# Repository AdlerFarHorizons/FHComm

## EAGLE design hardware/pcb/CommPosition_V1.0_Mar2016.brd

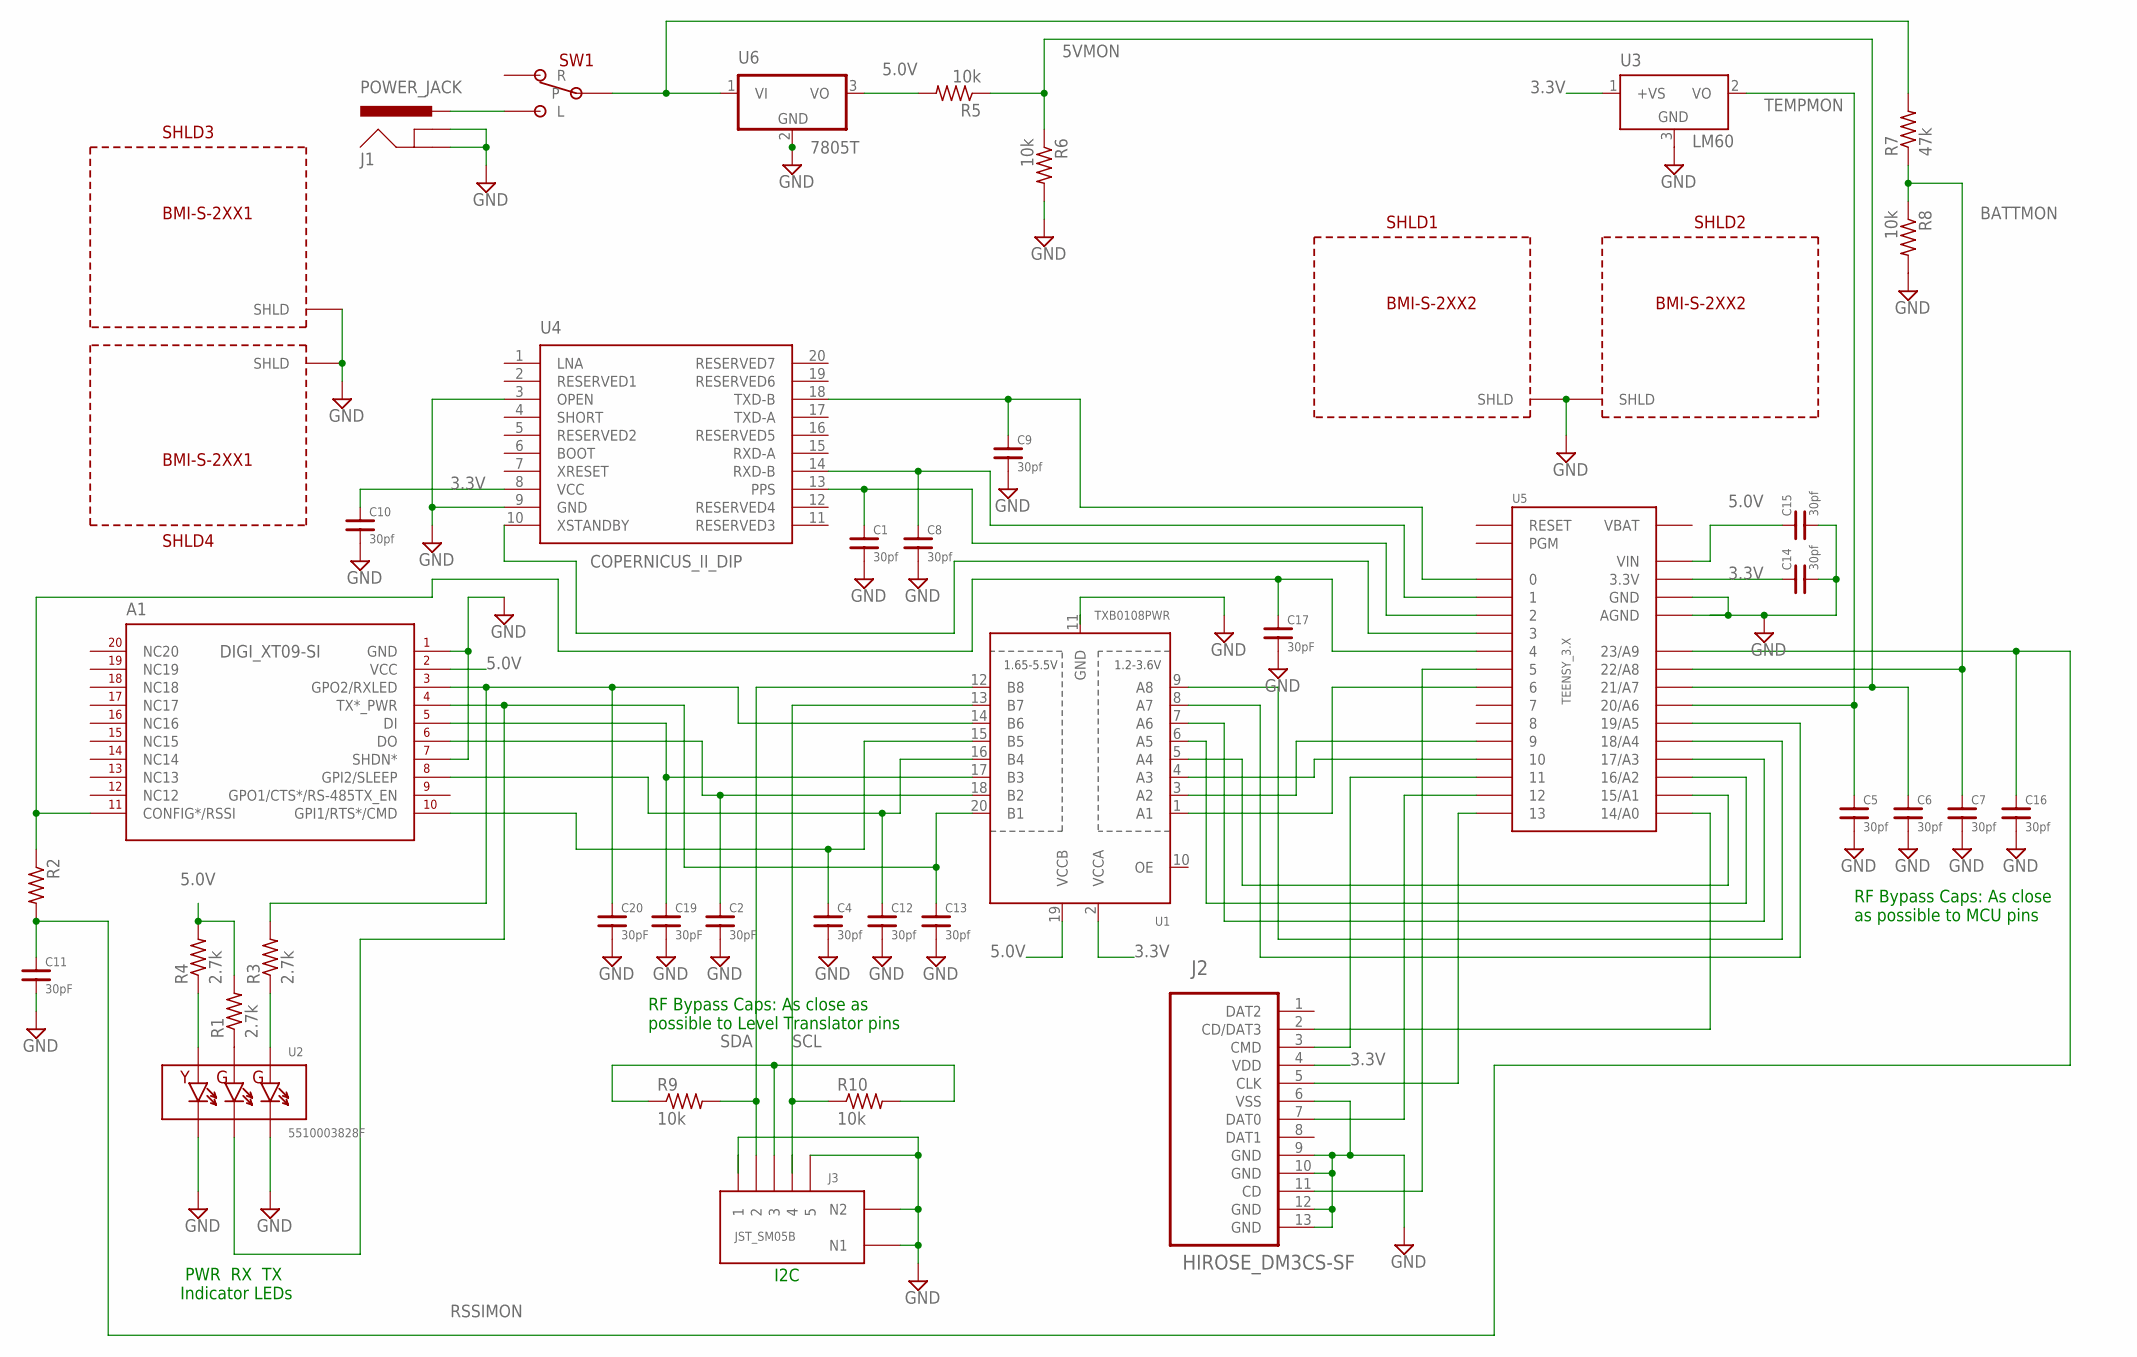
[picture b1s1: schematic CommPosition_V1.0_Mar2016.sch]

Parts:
A1: DIGI_XT09-SI
C1, C4, C5, C6, C7, C8, C9, C10, C12, C13, C14, C15, C16: 30pf; C0603
C2, C11, C17, C19, C20: 30pF; C0603
J1: POWER_JACK; PWR_JACK_BB
J2: HIROSE_DM3CS-SF
J3: JST_SM05B
R1, R3, R4: 2.7k; R0805
R2: R-US_R0805; R0805
R5, R6, R8, R9, R10: 10k; R0805
R7: 47k; R0805
SHLD1, SHLD2: BMI-S-2XX2; BMI-S-207-F
SHLD3, SHLD4: BMI-S-2XX1; BMI-S-206-F
SW1: SPDT_RA_3A; ESWITCH_SPDT_RA
U1: TXB0108PWR; TSSOP20
U2: 5510003828F; TRIPLE_LED_SIDE_0.1IN
U3: LM60; TO92
U4: COPERNICUS_II_DIP
U5: TEENSY_3.X; TEENSY_3.X_PERIPHERY
U6: 7805T; TO220H

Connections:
3.3V: C10.1, C14.1, J2.4 (VDD), U1.2 (VCCA), U3.1 (+VS), U4.8 (VCC), U5.3.3V, U5.3.3V1 (3.3V)
5.0V: A1.P$2 (VCC), C15.1, R1.2, R4.2, R5.2, U1.19 (VCCB), U5.VIN, U6.3 (VO)
5VMON: C6.1, R5.1, R6.1, U5.21/A7
BATTMON: C7.1, R7.1, R8.1, U5.22/A8
GND: A1.P$1 (GND), A1.P$7 (SHDN*), A1.P$21 (GND), A1.P$22 (GND), A1.P$23 (GND), A1.P$24 (GND), C1.2, C2.2, C4.2, C5.2, C6.2, C7.2, C8.2, C9.2, C10.2, C11.2, C12.2, C13.2, C14.2, C15.2, C16.2, C17.2, C19.2, C20.2, J1.GND, J1.GNDBREAK, J2.6 (VSS), J2.9 (GND), J2.10 (GND), J2.12 (GND), J2.13 (GND), J3.P$1 (1), J3.P$5 (5), J3.P$6 (N1), J3.P$7 (N2), R6.2, R8.2, SHLD1.P$2, SHLD1.P$3, SHLD1.P$4, SHLD1.P$5, SHLD1.P$6, SHLD1.P$7, SHLD1.P$8, SHLD1.P$9, SHLD1.P$10, SHLD1.P$11, SHLD1.P$12, SHLD1.P$14, SHLD1.P$15, SHLD1.P$16, SHLD1.P$17, SHLD1.P$18, SHLD1.P$19, SHLD1.P$20, SHLD1.P$21, SHLD1.P$22, SHLD1.P$23, SHLD1.P$24, SHLD1.P$25, SHLD1.P$26, SHLD1.P$27, SHLD1.P$28, SHLD1.P$29, SHLD1.P$30, SHLD1.P$31, SHLD1.P$32, SHLD1.P$33, SHLD1.P$34, SHLD2.P$2, SHLD2.P$3, SHLD2.P$4, SHLD2.P$5, SHLD2.P$6, SHLD2.P$7, SHLD2.P$8, SHLD2.P$9, SHLD2.P$10, SHLD2.P$11, SHLD2.P$12, SHLD2.P$14, SHLD2.P$15, SHLD2.P$16, SHLD2.P$17, SHLD2.P$18, SHLD2.P$19, SHLD2.P$20, SHLD2.P$21, SHLD2.P$22, SHLD2.P$23, SHLD2.P$24, SHLD2.P$25, SHLD2.P$26, SHLD2.P$27, SHLD2.P$28, SHLD2.P$29, SHLD2.P$30, SHLD2.P$31, SHLD2.P$32, SHLD2.P$33, SHLD2.P$34, SHLD3.P$1, SHLD3.P$2, SHLD3.P$3, SHLD3.P$4, SHLD3.P$5, SHLD3.P$6, SHLD3.P$7, SHLD3.P$8, SHLD3.P$9, SHLD3.P$10, SHLD3.P$11, SHLD3.P$12, SHLD3.P$14, SHLD3.P$15, SHLD3.P$16, SHLD3.P$17, SHLD3.P$18, SHLD3.P$21, SHLD3.P$22, SHLD3.P$23, SHLD3.P$24, SHLD3.P$25, SHLD3.P$31, SHLD3.P$32, SHLD4.P$1, SHLD4.P$2, SHLD4.P$3, SHLD4.P$4, SHLD4.P$5, SHLD4.P$6, SHLD4.P$7, SHLD4.P$8, SHLD4.P$9, SHLD4.P$10, SHLD4.P$11, SHLD4.P$12, SHLD4.P$14, SHLD4.P$15, SHLD4.P$16, SHLD4.P$17, SHLD4.P$18, SHLD4.P$21, SHLD4.P$22, SHLD4.P$23, SHLD4.P$24, SHLD4.P$25, SHLD4.P$31, SHLD4.P$32, U1.11 (GND), U2.P$1 (1), U2.P$5 (5), U3.3 (GND), U4.3 (OPEN), U4.9 (GND), U5.AGND, U5.GND, U5.GND1 (GND), U6.2 (GND)
unnamed: J2.7 (DAT0), U5.12
unnamed: J2.3 (CMD), U5.11
unnamed: J2.5 (CLK), U5.13
unnamed: U1.3 (A2), U5.9
unnamed: A1.P$5 (DI), C19.1, U1.17 (B3)
unnamed: U1.9 (A8), U5.18/A4
unnamed: J2.2 (CD/DAT3), U5.14/A0
unnamed: A1.P$6 (DO), C2.1, U1.18 (B2)
unnamed: U1.8 (A7), U5.19/A5
unnamed: A1.P$10 (GPI1/RTS*/CMD), C4.1, U1.15 (B5)
unnamed: A1.P$4 (TX*_PWR), C13.1, U1.20 (B1), U2.P$3 (3)
unnamed: A1.P$8 (GPI2/SLEEP), C12.1, U1.16 (B4)
unnamed: A1.P$3 (GPO2/RXLED), C20.1, R3.2, U1.14 (B6)
unnamed: U1.1 (A1), U5.6
unnamed: A1.P$11 (CONFIG*/RSSI), C17.1, R2.1, U5.4
unnamed: R7.2, SW1.P$2, U6.1 (VI)
unnamed: J1.PWR, SW1.P$1 (L)
unnamed: J2.11 (CD), U5.5
unnamed: U4.10 (XSTANDBY), U5.3
unnamed: J3.P$3 (3), R9.1, R10.2
unnamed: U1.5 (A4), U5.15/A1
unnamed: U1.6 (A5), U5.16/A2
unnamed: U1.4 (A3), U5.10
unnamed: U1.7 (A6), U5.17/A3
unnamed: C9.1, U4.18 (TXD-B), U5.0
unnamed: C8.1, U4.14 (RXD-B), U5.1
unnamed: C1.1, U4.13 (PPS), U5.2
unnamed: R1.1, U2.P$4 (4)
unnamed: R3.1, U2.P$2 (2)
unnamed: R4.1, U2.P$6 (6)
RSSIMON: C11.1, C16.1, R2.2, U5.23/A9
SCL: J3.P$4 (4), R10.1, U1.13 (B7)
SDA: J3.P$2 (2), R9.2, U1.12 (B8)
TEMPMON: C5.1, U3.2 (VO), U5.20/A6

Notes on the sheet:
RF Bypass Caps: As close as possible to MCU pins
PWR RX TX Indicator LEDs
RF Bypass Caps: As close as possible to Level Translator pins
I2C

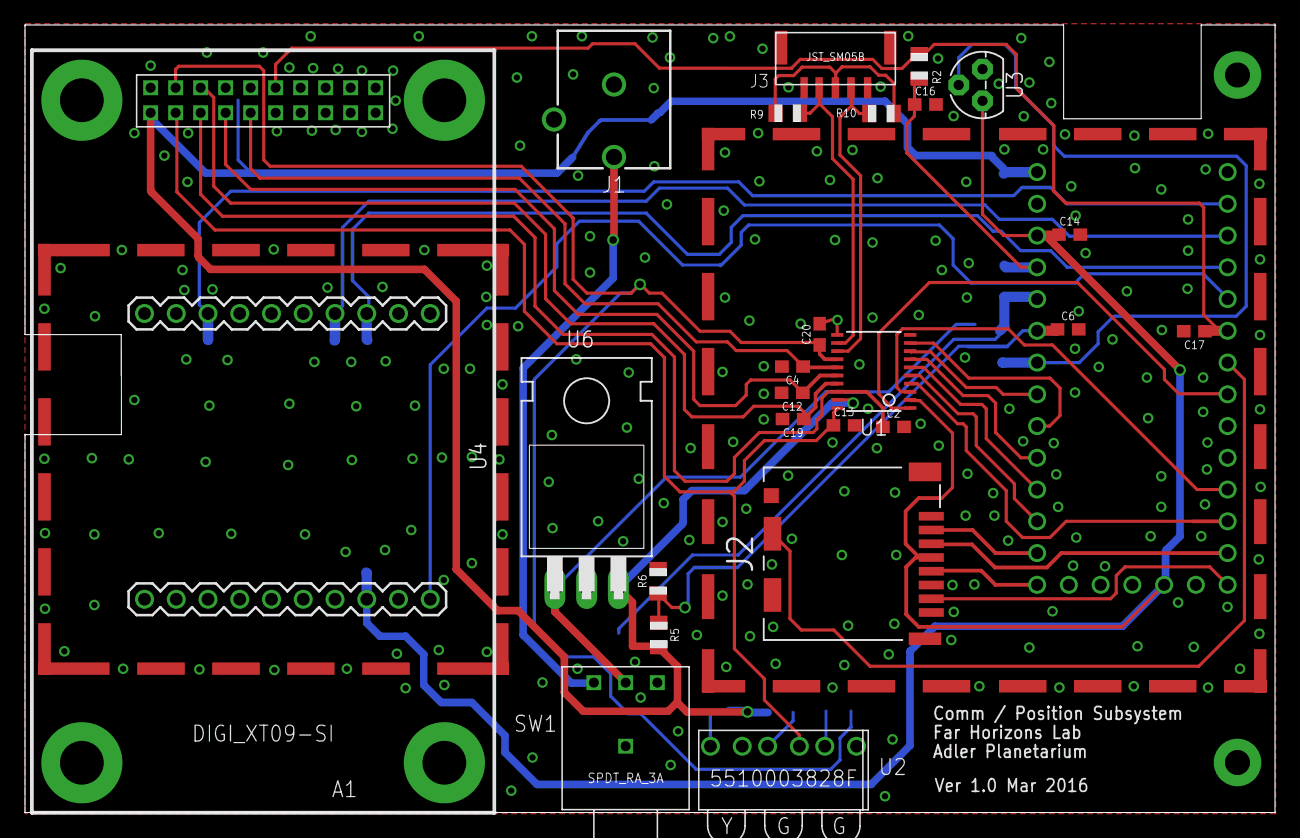
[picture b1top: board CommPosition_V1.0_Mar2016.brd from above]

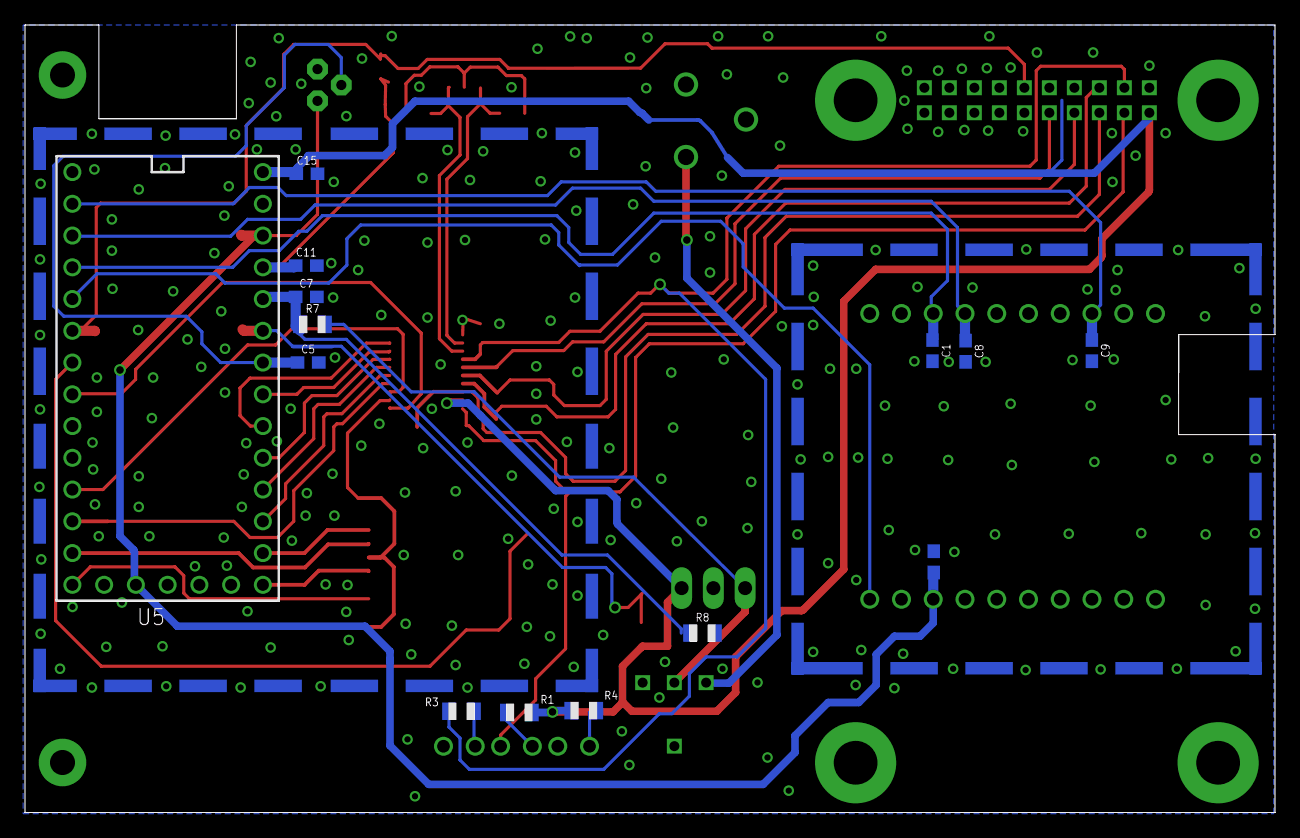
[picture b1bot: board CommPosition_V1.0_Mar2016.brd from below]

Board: 2 copper layers, 100.0 x 63.0 mm, 43 parts (16 on the bottom side), 39 nets.

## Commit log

2016-10-24 Initial commit from XTendGroundTeensy and XTendPayloadTeensy code in Transceiver project.
2017-01-06 Re-arrange and simplify round-robin loop; Update flowchart (still incomplete). Flag checking order in loop had included sequential tasks.
2017-01-28 Deleting temp file
2017-03-28 Command infrastructure and single uplink command capability;LOS calc doc
2017-07-23 Fix output power for field use
2017-11-22 Basic Command infrastructure; crude single uplink command with relay to OBC and response back down to ground.
2017-11-22 Finally adding .gitignore
2018-01-21 Housekeeping; Eliminate redundant checksum; Prevent RX array overrun.
2018-01-21 Add payload background spectrum measure; Extend payload transceiver wake time for ground response; Add payload spectrum display to ground monitor.
2018-01-27 Add a ruby client cabable of ftp-like download
2018-01-27 Incorporate CLI library with ftp-like capability
2018-02-14 Housekeeping
2018-02-14 Incorporate CLI library with ftp-like capability in Payload
2018-02-14 Version info; GPS timeout; log file data header.
2018-03-31 Fix command mode lockup if CR is entered alone; Echo mode modifications.
2018-05-26 Enable XBee interface
2018-06-13 Basic intra-payload messaging; Reduce terminal output
